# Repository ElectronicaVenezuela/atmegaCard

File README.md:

# Algo para desarrollar proyectos rapidito con el atmega328

La funcion basica es ayudar al desarrollo de proyectos en los que se requiera una gran cantidad de perifericos, ademas de esto, tambien cuenta con comunicacion wifi y en futuras versiones se piensa implementar comunicacion Ethernet.

## Autor:
Esteban el de la UNET XD

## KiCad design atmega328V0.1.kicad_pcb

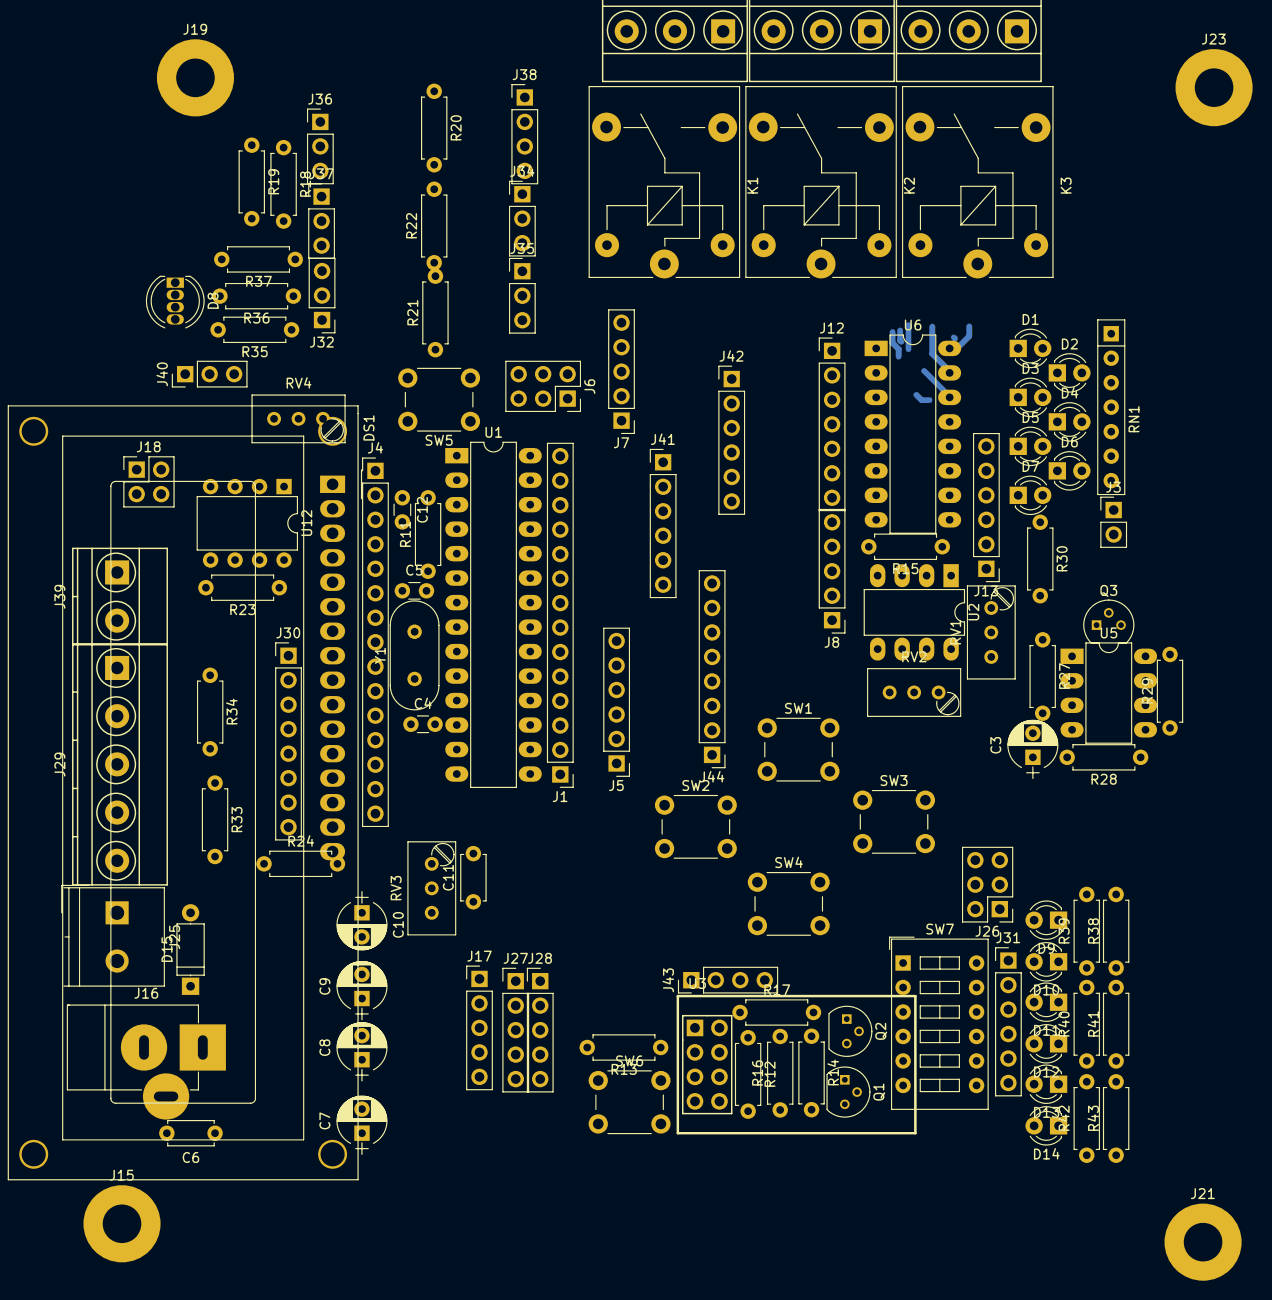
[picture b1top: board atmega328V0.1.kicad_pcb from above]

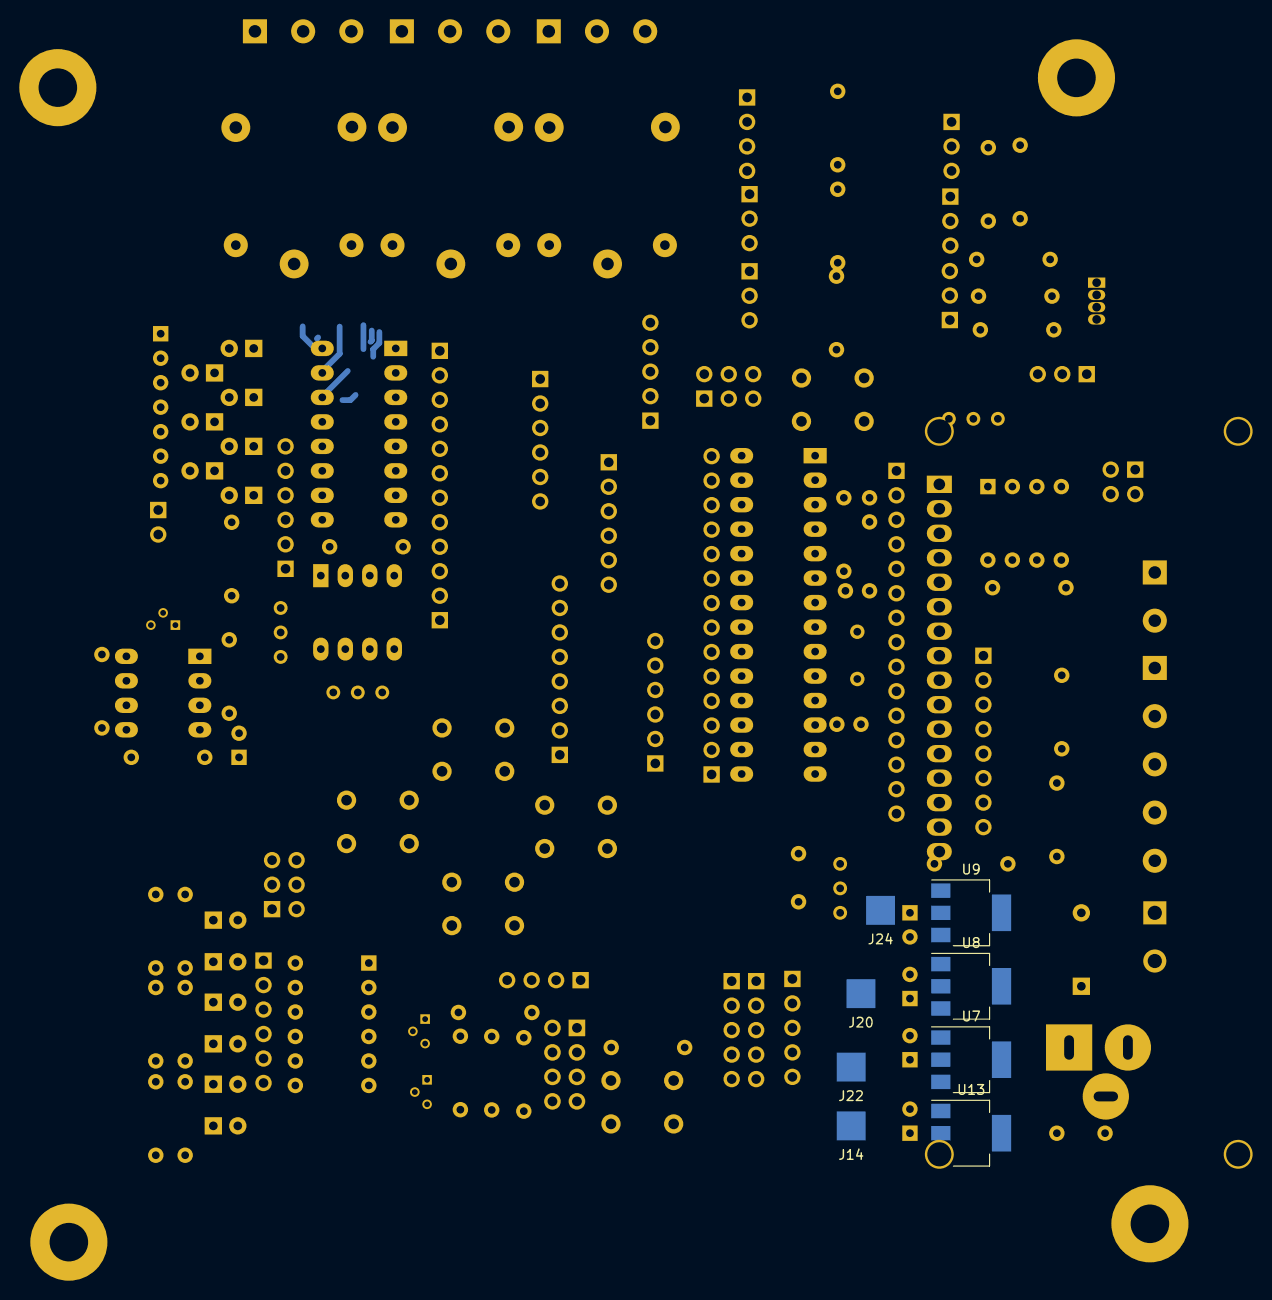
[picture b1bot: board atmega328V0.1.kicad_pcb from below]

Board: 2 copper layers, 126 parts (8 on the bottom side), 116 nets.

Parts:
C3: 1uF/16V; CP_Radial_D5.0mm_P2.50mm
C4, C5, C12: 22pF; C_Disc_D3.0mm_W1.6mm_P2.50mm
C6, C11: 100nF; C_Disc_D4.7mm_W2.5mm_P5.00mm
C7, C8, C9, C10: 47uF/16V; CP_Radial_D5.0mm_P2.50mm
D1, D2, D3, D4, D5, D6, D7: LEDO; LED_D3.0mm
D8: LED_RAGB; LED_D5.0mm-4
D9, D10, D11, D12, D13, D14: LED; LED_D3.0mm
D15: 1N4007; D_A-405_P7.62mm_Horizontal
DS1: WC1602A
J1: DO; Socket_Strip_Straight_1x14_Pitch2.54mm
J3: SPKR; Socket_Strip_Straight_1x02_Pitch2.54mm
J4: DO; Socket_Strip_Straight_1x15_Pitch2.54mm
J5: SD_CARD; Socket_Strip_Straight_1x06_Pitch2.54mm
J6: ICSP; Socket_Strip_Straight_2x03_Pitch2.54mm
J7: I2C; Socket_Strip_Straight_1x05_Pitch2.54mm
J8: OPAMP; Socket_Strip_Straight_1x05_Pitch2.54mm
J9, J11: REL1; TerminalBlock_Phoenix_MKDS1.5-3pol
J10: REL2; TerminalBlock_Phoenix_MKDS1.5-3pol
J12: DARL_IN; Socket_Strip_Straight_1x07_Pitch2.54mm
J13: DARL_OUT; Socket_Strip_Straight_1x06_Pitch2.54mm
J14: 12V; Measurement_Point_Square-SMD-Pad_Big
J15, J19, J21, J23: MH; MountingHole_4mm_Pad
J16: DC-INPUT; JACK_ALIM
J17: SUPPLY_SOCKET; Socket_Strip_Straight_1x05_Pitch2.54mm
J18: VCC; Pin_Header_Straight_2x02_Pitch2.54mm
J20: 5V; Measurement_Point_Square-SMD-Pad_Big
J22: 3V3; Measurement_Point_Square-SMD-Pad_Big
J24: ADJ; Measurement_Point_Square-SMD-Pad_Big
J25: BAT; TerminalBlock_Philmore_TB132_02x5mm_Straight
J26: VAA; Pin_Header_Straight_2x03_Pitch2.54mm
J27: SUPPLY_PIN; Pin_Header_Straight_1x05_Pitch2.54mm
J28: SUPPLY_ANGLED; Socket_Strip_Straight_1x05_Pitch2.54mm
J29: SUPPLY_TB; TerminalBlock_Phoenix_MKDS1.5-5pol
J30: NOKIA5110; Socket_Strip_Straight_1x08_Pitch2.54mm
J31: DIGITAL_INPUT; Socket_Strip_Straight_1x06_Pitch2.54mm
J32: RGB; Socket_Strip_Straight_1x03_Pitch2.54mm
J34: THERMISTOR; Socket_Strip_Straight_1x03_Pitch2.54mm
J35: LDR; Socket_Strip_Straight_1x03_Pitch2.54mm
J36, J37: 4-20mA; Socket_Strip_Straight_1x03_Pitch2.54mm
J38: ONE_WIRE; Socket_Strip_Straight_1x04_Pitch2.54mm
J39: BUS485; TerminalBlock_Phoenix_MKDS1.5-2pol
J40: 485TTL; Socket_Strip_Straight_1x03_Pitch2.54mm
J41: BT_HC05; Socket_Strip_Straight_1x06_Pitch2.54mm
J42: SIM800L; Socket_Strip_Straight_1x06_Pitch2.54mm
J43: ESP01; Socket_Strip_Straight_1x04_Pitch2.54mm
J44: RFID RC522; Socket_Strip_Straight_1x08_Pitch2.54mm
K1, K2, K3: SANYOU_SRD_Form_C; Relay_SPDT_SANYOU_SRD_Series_Form_C
Q1, Q2, Q3: 2N3904; TO-92_Molded_Narrow
R11, R12, R13, R14, R16, R17, R21, R22, R27: 10KΩ; R_Axial_DIN0207_L6.3mm_D2.5mm_P7.62mm_Horizontal
R15, R30: 1KΩ; R_Axial_DIN0207_L6.3mm_D2.5mm_P7.62mm_Horizontal
R18, R19: 250Ω; R_Axial_DIN0207_L6.3mm_D2.5mm_P7.62mm_Horizontal
R20: 4K7Ω; R_Axial_DIN0207_L6.3mm_D2.5mm_P7.62mm_Horizontal
R23, R29, R34: 120Ω; R_Axial_DIN0207_L6.3mm_D2.5mm_P7.62mm_Horizontal
R24: 120; R_Axial_DIN0207_L6.3mm_D2.5mm_P7.62mm_Horizontal
R28: 2KΩ; R_Axial_DIN0207_L6.3mm_D2.5mm_P7.62mm_Horizontal
R33: 680Ω; R_Axial_DIN0207_L6.3mm_D2.5mm_P7.62mm_Horizontal
R35, R36, R37: 300Ω; R_Axial_DIN0207_L6.3mm_D2.5mm_P7.62mm_Horizontal
R38, R39, R40, R41, R42, R43: 470Ω; R_Axial_DIN0207_L6.3mm_D2.5mm_P7.62mm_Horizontal
RN1: R_Network06; R_Array_SIP7
RV1: POT300K; Potentiometer_Trimmer_Bourns_3296W
RV2: POT10K; Potentiometer_Trimmer_Bourns_3296W
RV3: POT1K; Potentiometer_Trimmer_Bourns_3296W
RV4: P10K; Potentiometer_Trimmer_Bourns_3296W
SW1: OK; SW_PUSH_6mm
SW2: PREV; SW_PUSH_6mm
SW3: NEXT; SW_PUSH_6mm
SW4: BACK; SW_PUSH_6mm
SW5: RESET; SW_PUSH_6mm
SW6: RESETE; SW_PUSH_6mm
SW7: DIP_SW; SW_DIP_x6_W7.62mm_Slide
U1: ATMEGA328P-PU; DIP-28_W7.62mm_LongPads
U2: LM358; DIP-8_W7.62mm_LongPads
U3: ESP-01v090; ESP-01
U5: NE555; DIP-8_W7.62mm_LongPads
U6: ULN2004; DIP-16_W7.62mm_LongPads
U7: AP1117-33; SOT-223-3Lead_TabPin2
U8, U13: AP1117-50; SOT-223-3Lead_TabPin2
U9: AP1117-ADJ; SOT-223-3Lead_TabPin2
U12: MAX485E; DIP-8_W7.62mm
Y1: Crystal; Crystal_HC18-U_Vertical

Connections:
+3V3: C8.1, J5.1, J7.2, J17.3, J18.2, J22.1, J26.5, J27.3, J28.3, J29.3, J30.6, J44.8, R12.1, R13.1, R14.1, U3.3, U3.7, U7.2
+5V: C9.1, DS1.2, J6.2, J7.1, J17.2, J18.1, J20.1, J26.3, J27.2, J28.2, J29.2, J41.5, RV4.3, U8.2
+12V: C6.1, C7.1, D15.1, J13.1, J13.2, J13.3, J14.1, J16.1, J17.4, J26.1, J27.4, J28.4, J29.4, K1.5, K2.5, K3.5, R30.2, R33.1, R34.1, RN1.1, U6.9, U8.3, U9.3, U13.3
/2: J4.7, U1.4
/3: DS1.4, J4.8, J30.1, U1.5
/4: DS1.6, J4.9, J30.2, U1.6
/5: DS1.11, J4.12, J30.3, U1.11
/6: DS1.12, J4.13, J30.4, U1.12
/7: DS1.13, J4.14, J30.5, U1.13
/8: DS1.14, J4.15, SW2.1, U1.14
/9: J1.1, SW4.2, U1.15
/10: J1.2, J5.2, SW3.2, U1.16
/11: J1.3, J5.3, J6.4, J44.3, U1.17
/12: J1.4, J5.5, J6.1, J44.4, U1.18
/13: J1.5, J6.3, J44.2, SW1.2, U1.19
/A0: J1.9, U1.23
/A1: J1.10, U1.24
/A2: J1.11, U1.25
/A3: J1.12, U1.26
/A4: J1.13, J7.3, U1.27
/A5: J1.14, J7.4, U1.28
/AREF: J1.7, U1.21
/DTR: C12.1, J4.3
/GPIO0: J43.3, U3.6
/GPIO2: J43.2, U3.4
/IN_AMP: J8.4, U2.3
/IN_COMP: J8.2, U2.5
/MODE485: J40.2, U12.2, U12.3
/ONEWIRE: J38.2, J38.4, R20.2
/OUT_AMP: J8.5, RV1.2, U2.1
/OUT_COMP: J8.1, U2.7
/REF_COMP: J8.3, RV2.2, U2.6
/RESET: C12.2, J4.4, J6.5, R11.2, SW5.1, U1.1
/RST: R13.2, SW6.1, U3.5
/RX: J4.5, U1.2
/RX485: J40.3, U12.1
/RX_ESP: J43.4, R17.1
/TX: J4.6, U1.3
/TX485: J40.1, U12.4
/TX_ESP: J43.1, U3.1
/URXD: Q1.3, R12.2, U3.8
/XTAL1: C5.1, U1.9, Y1.2
/XTAL2: C4.1, U1.10, Y1.1
/display/LED1: D9.2, J31.1, SW7.12
/display/LED2: D10.2, J31.2, SW7.11
/display/LED3: D11.2, J31.3, SW7.10
/display/LED4: D12.2, J31.4, SW7.9
/display/LED5: D13.2, J31.5, SW7.8
/display/LED6: D14.2, J31.6, SW7.7
/output/BUZZER: J12.4, U6.4
/output/COM1: J9.2, K1.1
/output/COM2: J10.2, K2.1
/output/COM3: J11.2, K3.1
/output/NC1: J9.1, K1.3
/output/NC2: J10.1, K2.3
/output/NC3: J11.1, K3.3
/output/NO1: J9.3, K1.4
/output/NO2: J10.3, K2.4
/output/NO3: J11.3, K3.4
/output/O1: D1.1, K1.2, U6.16
/output/O2: D2.1, K2.2, U6.15
/output/O3: D3.1, K3.2, U6.14
/output/O4: C3.2, D4.1, Q3.1, U5.1, U6.13
/output/O5: D5.1, J13.6, U6.12
/output/O6: D6.1, J13.5, U6.11
/output/O7: D7.1, J13.4, U6.10
/output/REL1: J12.1, U6.1
/output/REL2: J12.2, U6.2
/output/REL3: J12.3, U6.3
/output/SPKR: J3.2, Q3.3
/output/TR: C3.1, R28.2, U5.2, U5.6
GND: C4.2, C5.2, C6.2, C7.2, C8.2, C9.2, C10.2, C11.2, DS1.1, DS1.5, DS1.16, J1.8, J4.1, J4.11, J5.6, J6.6, J7.5, J16.2, J16.3, J17.5, J25.1, J27.5, J28.5, J29.5, J30.8, J36.3, J37.3, J38.3, J41.4, J42.6, J44.6, Q1.1, Q2.1, R15.2, R18.2, R19.2, R21.2, R22.2, R38.1, R39.1, R40.1, R41.1, R42.1, R43.1, RV2.3, RV3.2, RV4.1, SW1.1, SW2.2, SW3.1, SW4.1, SW5.2, SW6.2, U1.8, U1.22, U2.4, U3.2, U6.8, U7.1, U8.1, U12.5, U13.1
unnamed: C11.1, R24.2, RV3.3, U9.1
unnamed: D1.2, RN1.2
unnamed: D2.2, RN1.3
unnamed: D3.2, RN1.4
unnamed: D4.2, RN1.5
unnamed: D5.2, RN1.6
unnamed: D6.2, RN1.7
unnamed: D7.2, R30.1
unnamed: D8.1, R37.2
unnamed: D8.3, R36.2
unnamed: D8.4, R35.2
unnamed: D9.1, R38.2
unnamed: D10.1, R39.2
unnamed: D11.1, R40.2
unnamed: D12.1, R41.2
unnamed: D13.1, R42.2
unnamed: D14.1, R43.2
unnamed: D15.2, J25.2
unnamed: DS1.3, RV4.2
unnamed: DS1.15, R33.2
unnamed: J12.5, U6.5
unnamed: J12.6, U6.6
unnamed: J12.7, U6.7
unnamed: J30.7, R34.2
unnamed: J32.1, R35.1
unnamed: J32.2, R36.1
unnamed: J32.3, R37.1
unnamed: J34.2, J34.3, R21.1
unnamed: J35.2, J35.3, R22.1
unnamed: J36.1, J36.2, R18.1
unnamed: J37.1, J37.2, R19.1
unnamed: J39.1, R23.1, U12.7
unnamed: J39.2, R23.2, U12.6
unnamed: Q1.2, R16.2
unnamed: Q2.2, R17.2
unnamed: Q2.3, R14.2, R16.1
unnamed: Q3.2, R27.1
unnamed: R15.1, RV1.1, U2.2
unnamed: R27.2, U5.3
unnamed: R28.1, R29.2, U5.7
unnamed: U7.3, U13.2
VAA: J3.1, J26.2, J26.4, J26.6, R29.1, RV2.1, U2.8, U5.4, U5.8
VCC: D8.2, J1.6, J4.2, J4.10, J18.3, J18.4, J34.1, J35.1, J38.1, R11.1, R20.1, SW7.1, SW7.2, SW7.3, SW7.4, SW7.5, SW7.6, U1.7, U1.20, U12.8
VDDA: C10.1, J17.1, J24.1, J27.1, J28.1, J29.1, J42.2, R24.1, U9.2

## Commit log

2018-08-17 primer commit
2018-08-20 agregando gitignore
2018-08-20 agregando README
